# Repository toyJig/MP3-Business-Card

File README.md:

This is one of the projects I've taken on to learn electronics and PCB design more in-depth. I had a career fair coming up, and I've always seen those guys on the internet with sick interactive custom-PCB business cards. So I thought, I want one too! Little did I know, this prroject wouldn't turn out as I had hoped with the battery constraints, but It's still something I'm relatiively proud of and can (hopefully) give out to recruiters- but only those I'm actually interested in since these are going to cost like 10$ each. If you got one from me, congrats? Hope it doesn't explode in your pocket haha

I really wanted this project to become a business card with what I imagined to just be a coin battery for the source. However, I soon found out that the max current draw on coin batteries is little to none compared to even running a single rp2040. The LiPo coin batteries looked promising but they're sort of out of my budget. So... LiPo pouch it is. 

(get the Toby Fox reference?)

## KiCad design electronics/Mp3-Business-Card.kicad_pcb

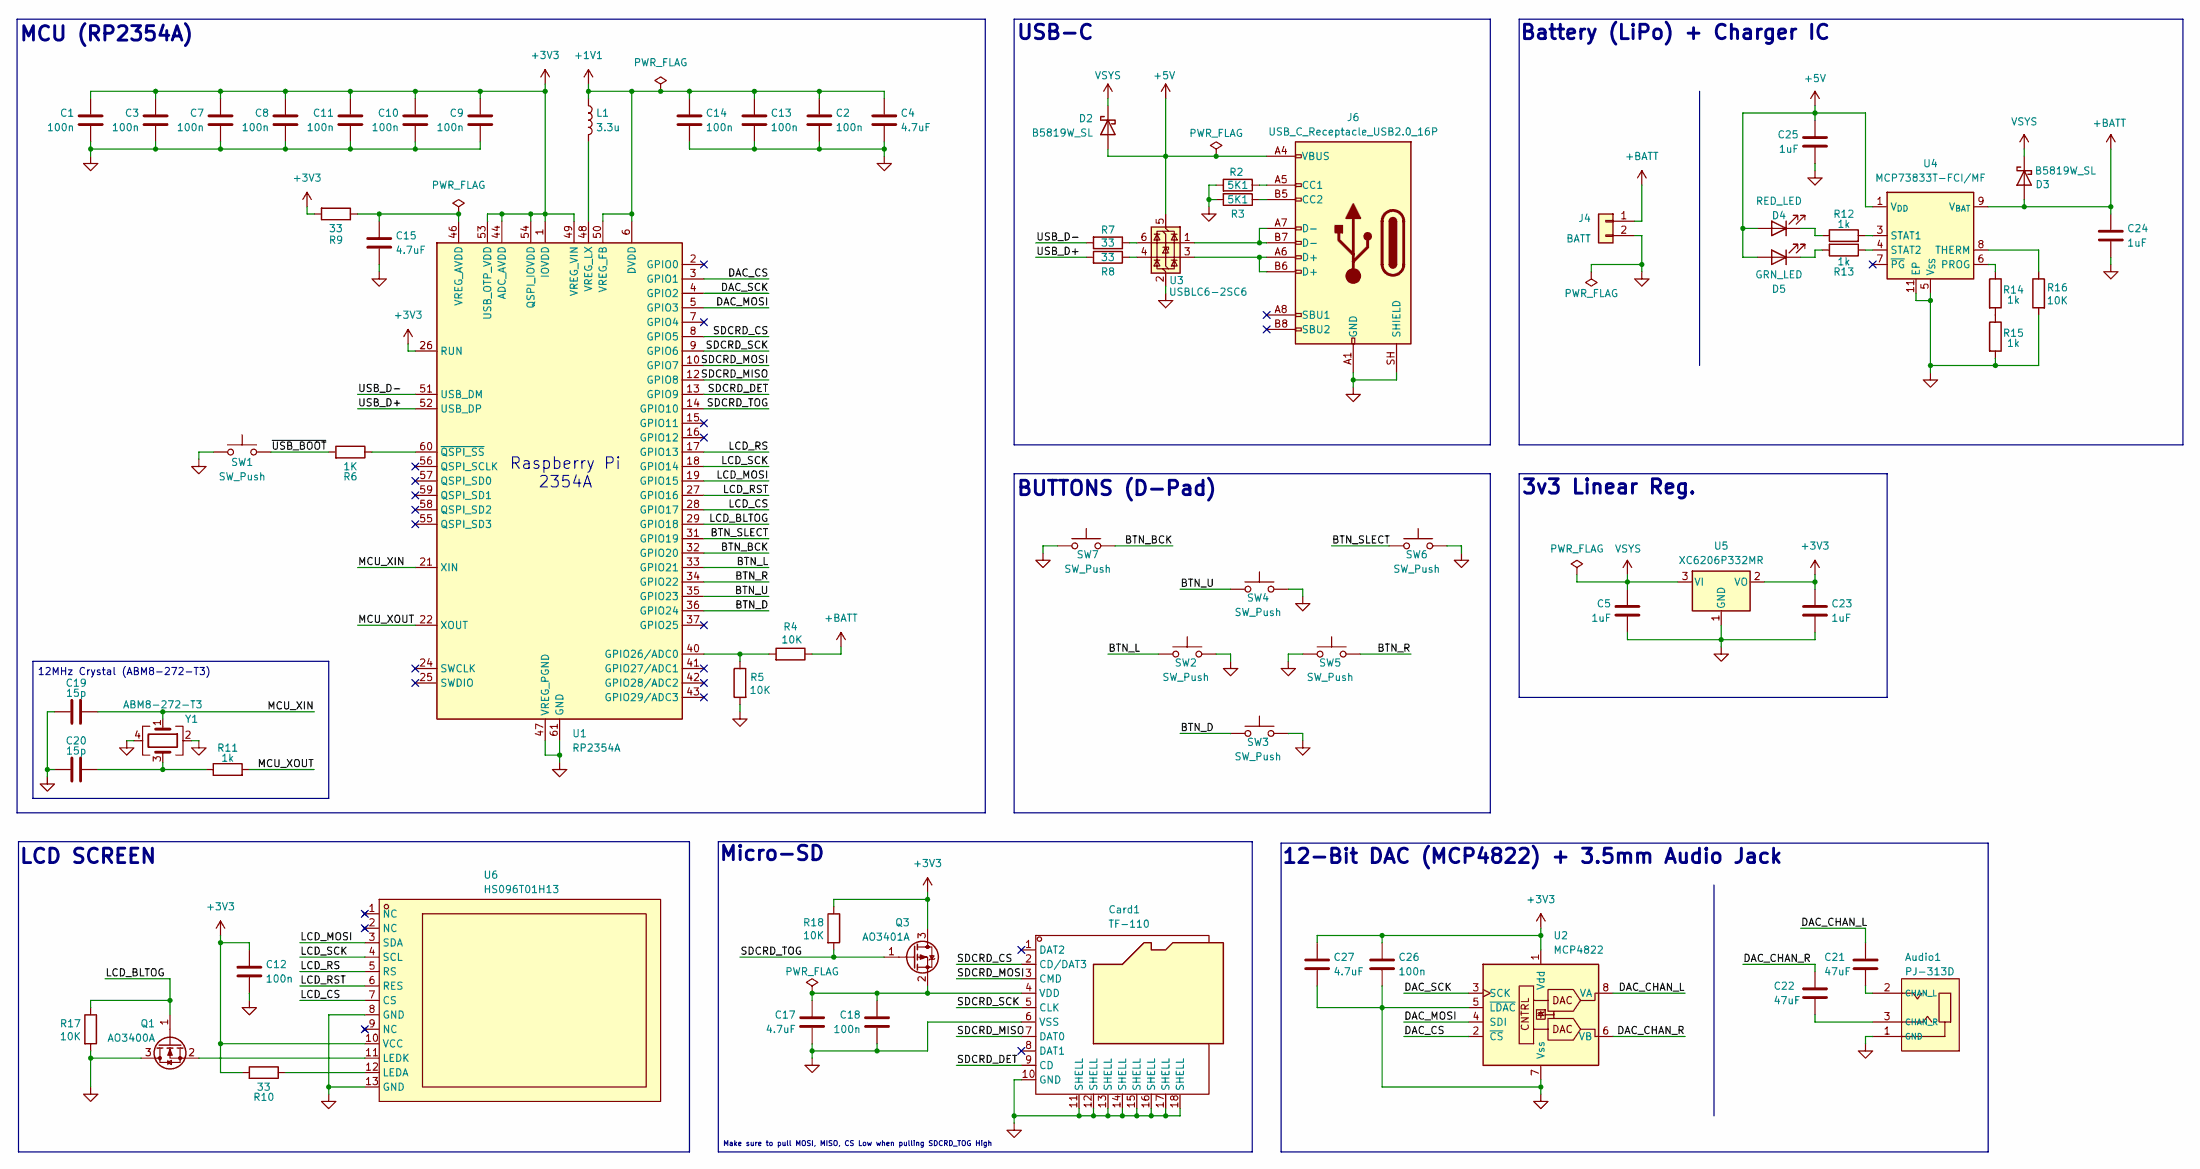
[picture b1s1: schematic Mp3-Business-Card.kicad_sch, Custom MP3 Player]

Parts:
Audio1: PJ-313D; AUDIO-SMD_PJ-313D; LCSC Part C95463
C1, C2, C3, C7, C8, C9, C10, C11, C12, C13, C14, C18, C26: 100n; C_0402_1005Metric; LCSC C1525
C4, C15, C17, C27: 4.7uF; C_0402_1005Metric; LCSC C1525
C5, C23, C24, C25: 1uF; C_0402_1005Metric; LCSC C1525
C19, C20: 15p; C_0402_1005Metric
C21, C22: 47uF; C_0402_1005Metric; LCSC C1525
Card1: TF-110; TF-SMD_TF-110; LCSC Part C266613
D2, D3: B5819W_SL; D_SOD-123; LCSC C8598
D4: RED_LED; LED_0201_0603Metric
D5: GRN_LED; LED_0201_0603Metric
J4: BATT; TestPoint_2Pads_Pitch5.08mm_Drill1.3mm; LCSC C160315
J6: USB_C_Receptacle_USB2.0_16P; USB_C_Receptacle_GCT_USB4105-xx-A_16P_TopMnt_Horizontal; LCSC C3025063
L1: 3.3u; L_0402_1005Metric
Q1: AO3400A; SOT-23
Q3: AO3401A; SOT-23
R2, R3: 5K1; R_0402_1005Metric; LCSC C25905
R4, R5, R16, R17: 10K; R_0402_1005Metric; LCSC C25905
R6: 1K; R_0402_1005Metric; LCSC C11702
R7, R8, R9, R10: 33; R_0402_1005Metric; LCSC C11702
R11, R12, R13, R14, R15: 1k; R_0402_1005Metric
R18: 10K; R_0603_1608Metric; LCSC C25905
SW1: SW_Push; SW_SPST_TS-1088-xR025; LCSC C269272
SW2, SW3, SW4, SW5, SW6, SW7: SW_Push; SW-SMD_4P-L5.1-W5.1-P3.70-LS6.5-TL_H1.5; LCSC C269272
U1: RP2354A; QFN-60-1EP_7x7mm_P0.4mm_EP3.4x3.4mm
U2: MCP4822; SOIC-8_3.9x4.9mm_P1.27mm
U3: USBLC6-2SC6; SOT-23-6; LCSC C2827654
U4: MCP73833T-FCI/MF; DFN-10-1EP_3x3mm_P0.5mm_EP1.58x2.35mm
U5: XC6206P332MR; SOT-23-3
U6: HS096T01H13; LCD-SMD_HS096T01H13; LCSC Part C18198246
Y1: ABM8-272-T3; Crystal_SMD_3225-4Pin_3.2x2.5mm

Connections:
+1V1: C2.1, C4.1, C13.1, C14.1, L1.1, U1.6 (DVDD), U1.23 (DVDD), U1.39 (DVDD), U1.50 (VREG_FB)
+3V3: C1.1, C3.1, C7.1, C8.1, C9.1, C10.1, C11.1, C12.1, C23.1, C26.1, C27.1, Q3.3 (D), R9.2, R10.2, R18.1, U1.1 (IOVDD), U1.11 (IOVDD), U1.20 (IOVDD), U1.26 (RUN), U1.30 (IOVDD), U1.38 (IOVDD), U1.44 (ADC_AVDD), U1.45 (IOVDD), U1.49 (VREG_VIN), U1.53 (USB_OTP_VDD), U1.54 (QSPI_IOVDD), U2.1 (Vdd), U5.2 (VO), U6.10 (VCC)
+5V: C25.1, D2.2 (A), D4.2 (A), D5.2 (A), J6.A4 (VBUS), J6.A9 (VBUS), J6.B4 (VBUS), J6.B9 (VBUS), U3.5 (VBUS), U4.1 (V_{DD}), U4.2 (V_{DD})
+BATT: C24.1, D3.2 (A), J4.1, R4.1, U4.9 (V_{BAT}), U4.10 (V_{BAT})
/BTN_BCK: SW7.1, U1.32 (GPIO20)
/BTN_D: SW3.1, U1.36 (GPIO24)
/BTN_L: SW2.1, U1.33 (GPIO21)
/BTN_R: SW5.2, U1.34 (GPIO22)
/BTN_SLECT: SW6.1, U1.31 (GPIO19)
/BTN_U: SW4.1, U1.35 (GPIO23)
/DAC_CHAN_L: C21.2, U2.8 (VA)
/DAC_CHAN_R: C22.2, U2.6 (VB)
/DAC_CS: U1.3 (GPIO1), U2.2 (~CS)
/DAC_MOSI: U1.5 (GPIO3), U2.4 (SDI)
/DAC_SCK: U1.4 (GPIO2), U2.3 (SCK)
/LCD_BLTOG: Q1.1 (G), R17.1, U1.29 (GPIO18)
/LCD_CS: U1.28 (GPIO17), U6.7 (CS)
/LCD_MOSI: U1.19 (GPIO15), U6.3 (SDA)
/LCD_RS: U1.17 (GPIO13), U6.5 (RS)
/LCD_RST: U1.27 (GPIO16), U6.6 (RES)
/LCD_SCK: U1.18 (GPIO14), U6.4 (SCL)
/MCU_XIN: C19.2, U1.21 (XIN), Y1.1
/MCU_XOUT: R11.2, U1.22 (XOUT)
/SDCRD_CS: Card1.2 (CD/DAT3), U1.8 (GPIO5)
/SDCRD_DET: Card1.9 (CD), U1.13 (GPIO9)
/SDCRD_MISO: Card1.7 (DAT0), U1.12 (GPIO8)
/SDCRD_MOSI: Card1.3 (CMD), U1.10 (GPIO7)
/SDCRD_SCK: Card1.5 (CLK), U1.9 (GPIO6)
/SDCRD_TOG: Q3.1 (G), R18.2, U1.14 (GPIO10)
/USB_D+: R8.2, U1.52 (USB_DP)
/USB_D-: R7.2, U1.51 (USB_DM)
/~USB_BOOT: R6.2, SW1.2
GND: Audio1.1 (GND), C1.2, C2.2, C3.2, C4.2, C5.2, C7.2, C8.2, C9.2, C10.2, C11.2, C12.2, C13.2, C14.2, C15.2, C17.2, C18.2, C19.1, C20.1, C23.2, C24.2, C25.2, C26.2, C27.2, Card1.6 (VSS), Card1.10 (GND), Card1.11 (SHELL), Card1.12 (SHELL), Card1.13 (SHELL), Card1.14 (SHELL), Card1.15 (SHELL), Card1.16 (SHELL), Card1.17 (SHELL), Card1.18 (SHELL), J4.2, J6.A1 (GND), J6.A12 (GND), J6.B1 (GND), J6.B12 (GND), J6.SH (SHIELD), Q1.3 (D), R2.2, R3.2, R5.2, R15.2, R16.2, R17.2, SW1.1, SW2.2, SW3.2, SW4.2, SW5.1, SW6.2, SW7.2, U1.47 (VREG_PGND), U1.61 (GND), U2.5 (~LDAC), U2.7 (Vss), U3.2 (GND), U4.5 (V_{SS}), U4.11 (EP), U5.1 (GND), U6.8 (GND), U6.13 (GND), Y1.2, Y1.4
unnamed: Audio1.2 (CHAN_L), C21.1
unnamed: Audio1.3 (CHAN_R), C22.1
unnamed: C20.2, R11.1, Y1.3
unnamed: C17.1, C18.1, Card1.4 (VDD), Q3.2 (S)
unnamed: D4.1 (K), R12.1
unnamed: D5.1 (K), R13.2
unnamed: J6.A5 (CC1), R2.1
unnamed: J6.B5 (CC2), R3.1
unnamed: J6.A6 (D+), J6.B6 (D+), U3.3 (I/O2)
unnamed: J6.A7 (D-), J6.B7 (D-), U3.1 (I/O1)
unnamed: Q1.2 (S), U6.11 (LEDK)
unnamed: R7.1, U3.6 (I/O1)
unnamed: R8.1, U3.4 (I/O2)
unnamed: R14.2, R15.1
unnamed: R4.2, R5.1, U1.40 (GPIO26/ADC0)
unnamed: C15.1, R9.1, U1.46 (VREG_AVDD)
unnamed: L1.2, U1.48 (VREG_LX)
unnamed: R6.1, U1.60 (~QSPI_SS)
unnamed: R14.1, U4.6 (PROG)
unnamed: R12.2, U4.3 (STAT1)
unnamed: R13.1, U4.4 (STAT2)
unnamed: R16.1, U4.8 (THERM)
unnamed: R10.1, U6.12 (LEDA)
VSYS: C5.1, D2.1 (K), D3.1 (K), U5.3 (VI)

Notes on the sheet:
Make sure to pull MOSI, MISO, CS Low when pulling SDCRD_TOG High
BUTTONS (D-Pad)
USB-C
Battery (LiPo) + Charger IC
MCU (RP2354A)
3v3 Linear Reg.
Raspberry Pi 2354A
12MHz Crystal (ABM8-272-T3)
12-Bit DAC (MCP4822) + 3.5mm Audio Jack
Micro-SD
LCD SCREEN

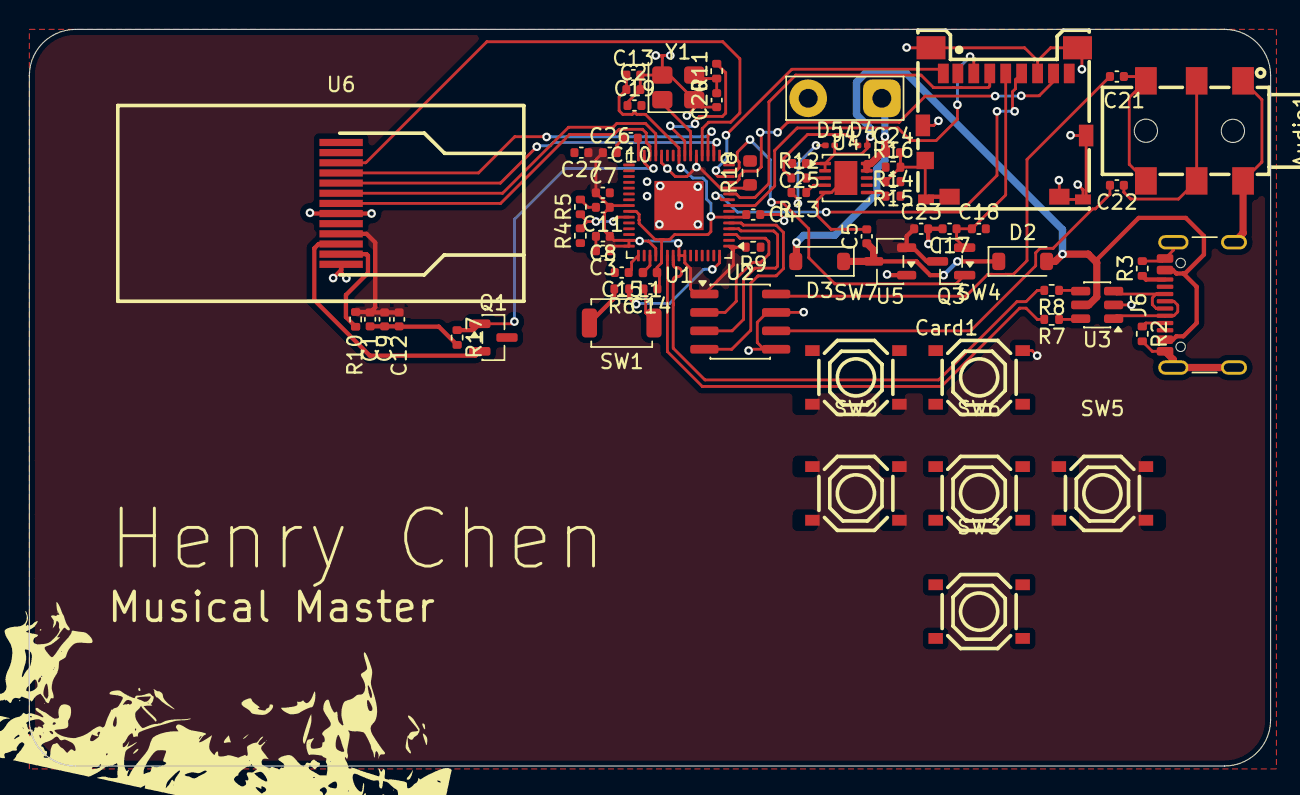
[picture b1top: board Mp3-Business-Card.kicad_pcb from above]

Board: 2 copper layers, 85.6 x 50.8 mm, 67 parts (0 on the bottom side), 57 nets.
